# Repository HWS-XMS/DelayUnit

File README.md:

# Precision Trigger Delay System

Configurable digital delay system for Xilinx FPGAs with 5ns resolution.

## Features

- **Resolution**: 5ns (200MHz clock)
- **Delay Range**: 0 to 21.5 seconds
- **Configurable Output Width**: 5ns to any duration
- **Control**: UART @ 1Mbaud with Python API
- **Supported Platforms**:
  - Digilent Arty A7-35T (XC7A35T)
  - Digilent Nexys Video (XC7A200T)

## Quick Start

### Build & Program

Navigate to your target board directory and use the local Makefile:

**For Arty A7:**
```bash
cd targets/arty
make synth         # Synthesize design
make program       # Program FPGA (volatile)
make flash         # Program SPI flash (persistent)
```

**For Nexys Video:**
```bash
cd targets/nexys
make synth         # Synthesize design
make program       # Program FPGA (volatile)
make flash         # Program SPI flash (persistent)
```

### Python Control

```python
from delay_unit import DelayUnit, EdgeType

with DelayUnit() as unit:
    unit.delay_ns = 100
    unit.width_ns = 50
    unit.soft_trigger()
    print(unit.status)
```

### Testing

```bash
cd python
python test_comprehensive.py  # 1000 test combinations
```

## Hardware Setup

### Arty A7-35T

**Soft Trigger Testing:**
- Jumper: JA Pin 3 → JA Pin 1
- Scope Ch1: JA Pin 3 (trigger)
- Scope Ch2: JA Pin 2 (delayed output)

**Pmod JA Pinout:**
- Pin 1 (G13): External trigger input
- Pin 2 (B11): Delayed trigger output
- Pin 3 (A11): Soft trigger output

### Nexys Video (XC7A200T)

**Soft Trigger Testing:**
- Jumper: JA Pin 3 → JA Pin 1
- Scope Ch1: JA Pin 3 (trigger)
- Scope Ch2: JA Pin 2 (delayed output)

**Pmod JA Pinout:**
- Pin 1 (AB22): External trigger input
- Pin 2 (AB21): Delayed trigger output
- Pin 3 (AB20): Soft trigger output

## Architecture

- **CDC_EDGE_DETECT**: Clock domain crossing with edge detection
- **CONFIGURABLE_DELAY**: Programmable delay with configurable output width
- **UART_RX/TX**: UART communication @ 1Mbaud
- **Clock**: 100MHz input → 200MHz system clock via MMCM

## UART Commands

| Command | Code | Data | Description |
|---------|------|------|-------------|
| SET_COARSE | 0x01 | 4 bytes | Set delay (cycles) |
| GET_COARSE | 0x02 | - | Get delay |
| SET_WIDTH | 0x08 | 4 bytes | Set output width (cycles) |
| GET_WIDTH | 0x09 | - | Get output width |
| SOFT_TRIGGER | 0x07 | - | Generate trigger |
| GET_STATUS | 0x05 | - | Get trigger count + delay |
| RESET_COUNT | 0x06 | - | Reset counter |

## License

MIT

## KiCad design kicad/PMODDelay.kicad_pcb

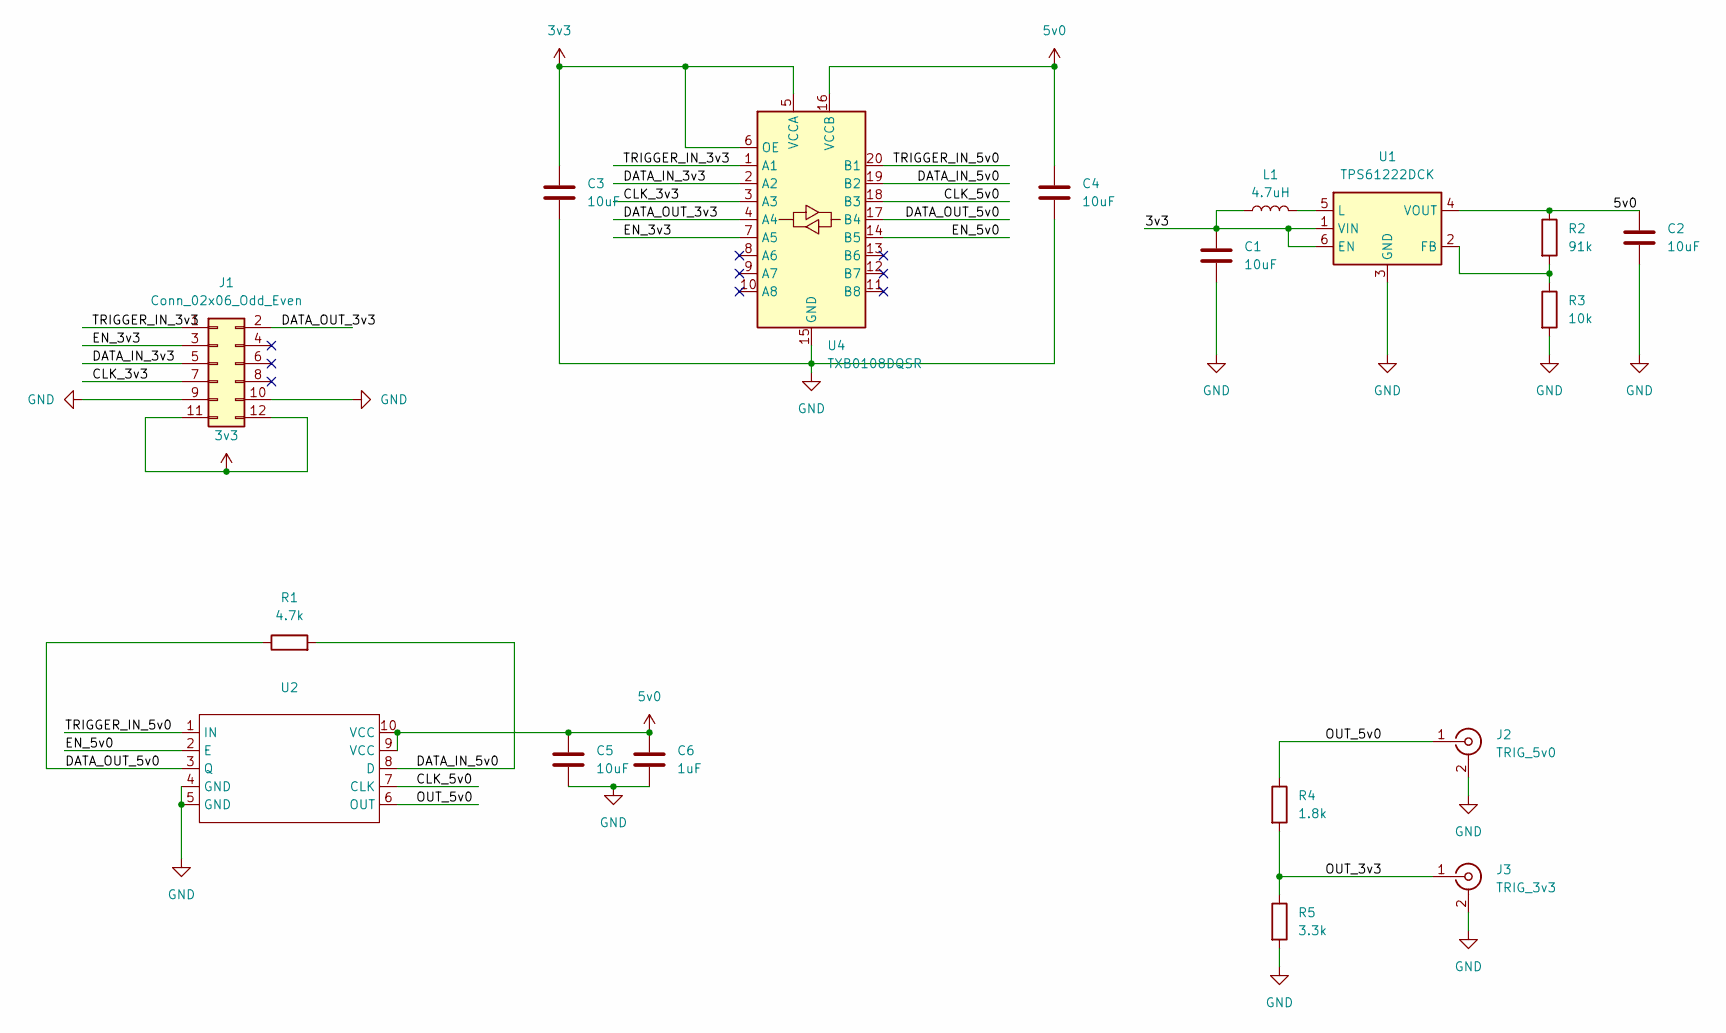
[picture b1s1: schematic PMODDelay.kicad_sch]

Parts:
C1, C2: 10uF; C_0805_2012Metric
C3, C4, C5: 10uF; C_0805_2012Metric_Pad1.18x1.45mm_HandSolder
C6: 1uF; C_0805_2012Metric_Pad1.18x1.45mm_HandSolder
J1: Conn_02x06_Odd_Even; PinHeader_2x06_P2.54mm_Horizontal
J2: TRIG_5v0; SMA_Amphenol_901-144_Vertical
J3: TRIG_3v3; SMA_Amphenol_901-144_Vertical
L1: 4.7uH; R_0805_2012Metric
R1: 4.7k; R_0805_2012Metric
R2: 91k; R_0805_2012Metric
R3: 10k; R_0805_2012Metric
R4: 1.8k; R_0805_2012Metric_Pad1.20x1.40mm_HandSolder
R5: 3.3k; R_0805_2012Metric_Pad1.20x1.40mm_HandSolder
U1: TPS61222DCK; Texas_R-PDSO-G6
U2: TSSOP-10_3x3mm_P0.5mm
U4: TXB0108DQSR; USON-20_2x4mm_P0.4mm

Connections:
3v3: C1.1, C3.1, J1.11, J1.12, L1.1, U1.1 (VIN), U1.6 (EN), U4.5 (VCCA), U4.6 (OE)
5v0: C2.1, C4.1, C5.1, C6.1, R2.1, U1.4 (VOUT), U2.9 (VCC), U2.10 (VCC), U4.16 (VCCB)
/CLK_3v3: J1.7, U4.3 (A3)
/CLK_5v0: U2.7 (CLK), U4.18 (B3)
/DATA_IN_3v3: J1.5, U4.2 (A2)
/DATA_IN_5v0: R1.2, U2.8 (D), U4.19 (B2)
/DATA_OUT_3v3: J1.2, U4.4 (A4)
/DATA_OUT_5v0: R1.1, U2.3 (Q), U4.17 (B4)
/EN_3v3: J1.3, U4.7 (A5)
/EN_5v0: U2.2 (E), U4.14 (B5)
/OUT_3v3: J3.1 (In), R4.2, R5.1
/OUT_5v0: J2.1 (In), R4.1, U2.6 (OUT)
/TRIGGER_IN_3v3: J1.1, U4.1 (A1)
/TRIGGER_IN_5v0: U2.1 (IN), U4.20 (B1)
GND: C1.2, C2.2, C3.2, C4.2, C5.2, C6.2, J1.9, J1.10, J2.2 (Ext), J3.2 (Ext), R3.2, R5.2, U1.3 (GND), U2.4 (GND), U2.5 (GND), U4.15 (GND)
unnamed: R2.2, R3.1, U1.2 (FB)
unnamed: L1.2, U1.5 (L)

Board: 2 copper layers, 18 parts (0 on the bottom side), 17 nets, no tracks yet.

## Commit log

2025-09-30 Picosecond-precision trigger delay system with MMCM
    - Implemented configurable digital delay with 20ps resolution
    - MMCM-based fine delay using 887.5MHz VCO (8.875x multiplier)
    - Coarse delay in clock cycles + fine delay in 20ps increments
    - Full 10ns coverage with clean 20ps steps
    - UART control interface with Python script
    - Support for edge detection (rising/falling/both)
2025-09-30 Fix: Use accurate 20.12ps resolution in calculations
    - Corrected step size from 20ps to 20.12ps (887.5MHz VCO / 56)
    - Updated FPGA calculation: steps = ps * 50 / 1006
    - Updated Python to match FPGA math exactly
    - Prevents overflow while maintaining precision
    - Max 497 steps for full 10ns range
2025-09-30 Reorganize project structure for better maintainability
    - Organized RTL into core/, mmcm/, uart/ subdirectories
    - Moved testbenches to tb/
    - Moved constraints to constraints/
    - Created scripts/ for vivado and python tools
    - Updated all include paths for new structure
    - Added comprehensive README with documentation
2025-09-30 Simplify project: focus on MMCM version for Xilinx only
    - Removed IceStick support (MMCM is Xilinx-specific)
    - Removed non-MMCM versions (keeping only 20ps precision version)
    - Removed unused docs directory
    - Renamed constraints to constraints_arty (board-specific)
    - Simplified Makefile and synthesis scripts
    - Updated README for streamlined structure
2025-09-30 Final restructuring and command renaming
    - Changed commands to SET_COARSE/GET_COARSE (not SET_DELAY/GET_DELAY)
    - Renamed constraints_arty to constraints (simpler)
    - Moved synth.tcl to top directory for easier access
    - Renamed scripts/ to python/ (contains only Python file)
    - Capitalized TRIGGER_DELAY_DEFS.vh header file
    - Updated all file paths and references
2025-09-30 Fix critical issues found in code review
    - Fixed module name from TRIGGER_DELAY_TOP_MMCM to TRIGGER_DELAY_TOP
    - Corrected VCO frequency comment (887.5MHz, not 1GHz)
    - Note: Simulation requires Xilinx tools for MMCM primitives
2025-10-01 Packaging
2025-10-03 Abandoning MMCM fine delay attempt
2025-10-05 Updating deprecated xilinx calls
2025-10-05 Adding Nexys-Video Support
2025-10-07 Introducing PMOD Delay Module
2025-10-09 Introducing DS1124U Driver, updating PCB.
2025-10-15 Add custom VID/PID support and FTDI EEPROM programming tools
2025-10-27 Introducing internal and external mode
2025-12-03 Add trigger counter mode
2025-12-04 Updating Schematic
2025-12-11 Adding sub-cycle delay support on FPGA instead of external module
